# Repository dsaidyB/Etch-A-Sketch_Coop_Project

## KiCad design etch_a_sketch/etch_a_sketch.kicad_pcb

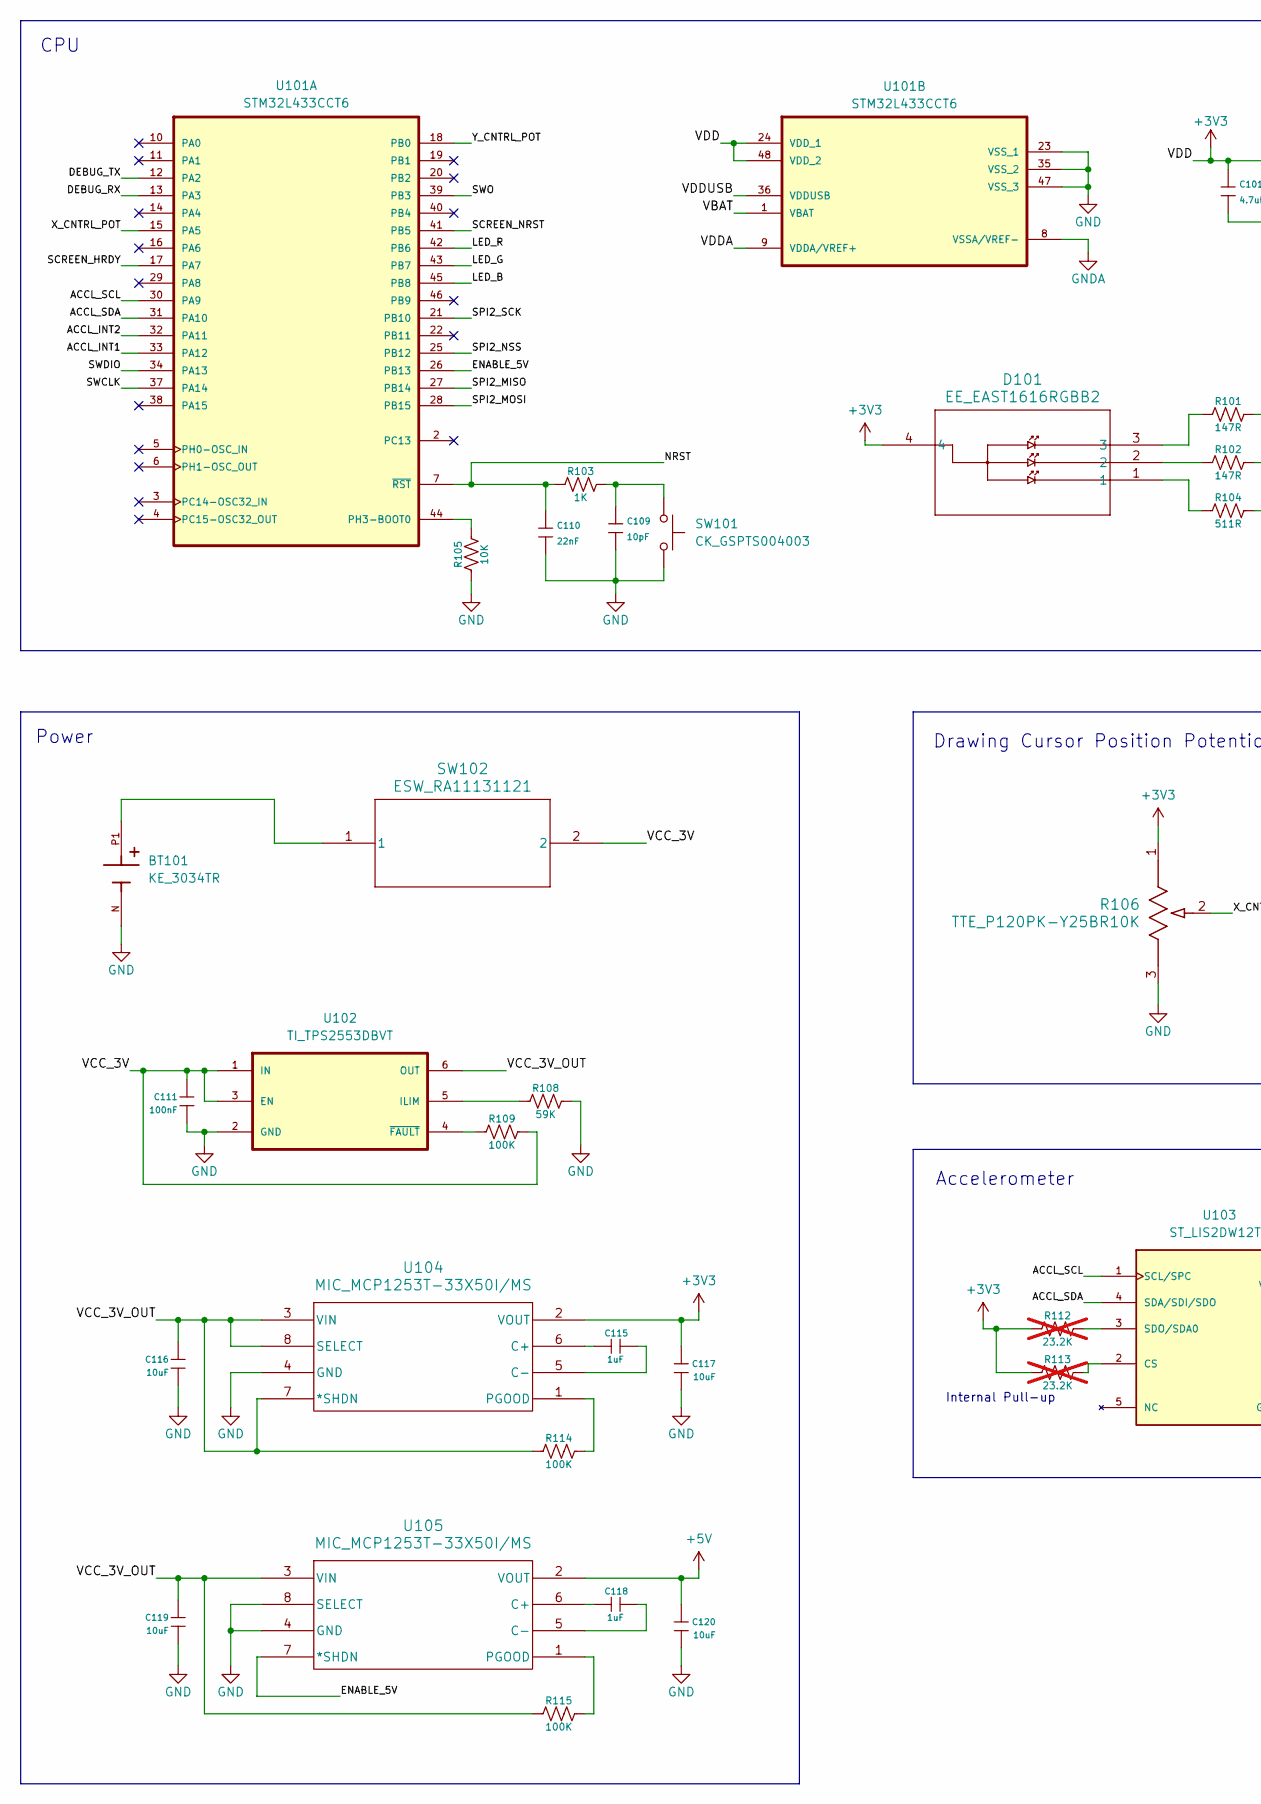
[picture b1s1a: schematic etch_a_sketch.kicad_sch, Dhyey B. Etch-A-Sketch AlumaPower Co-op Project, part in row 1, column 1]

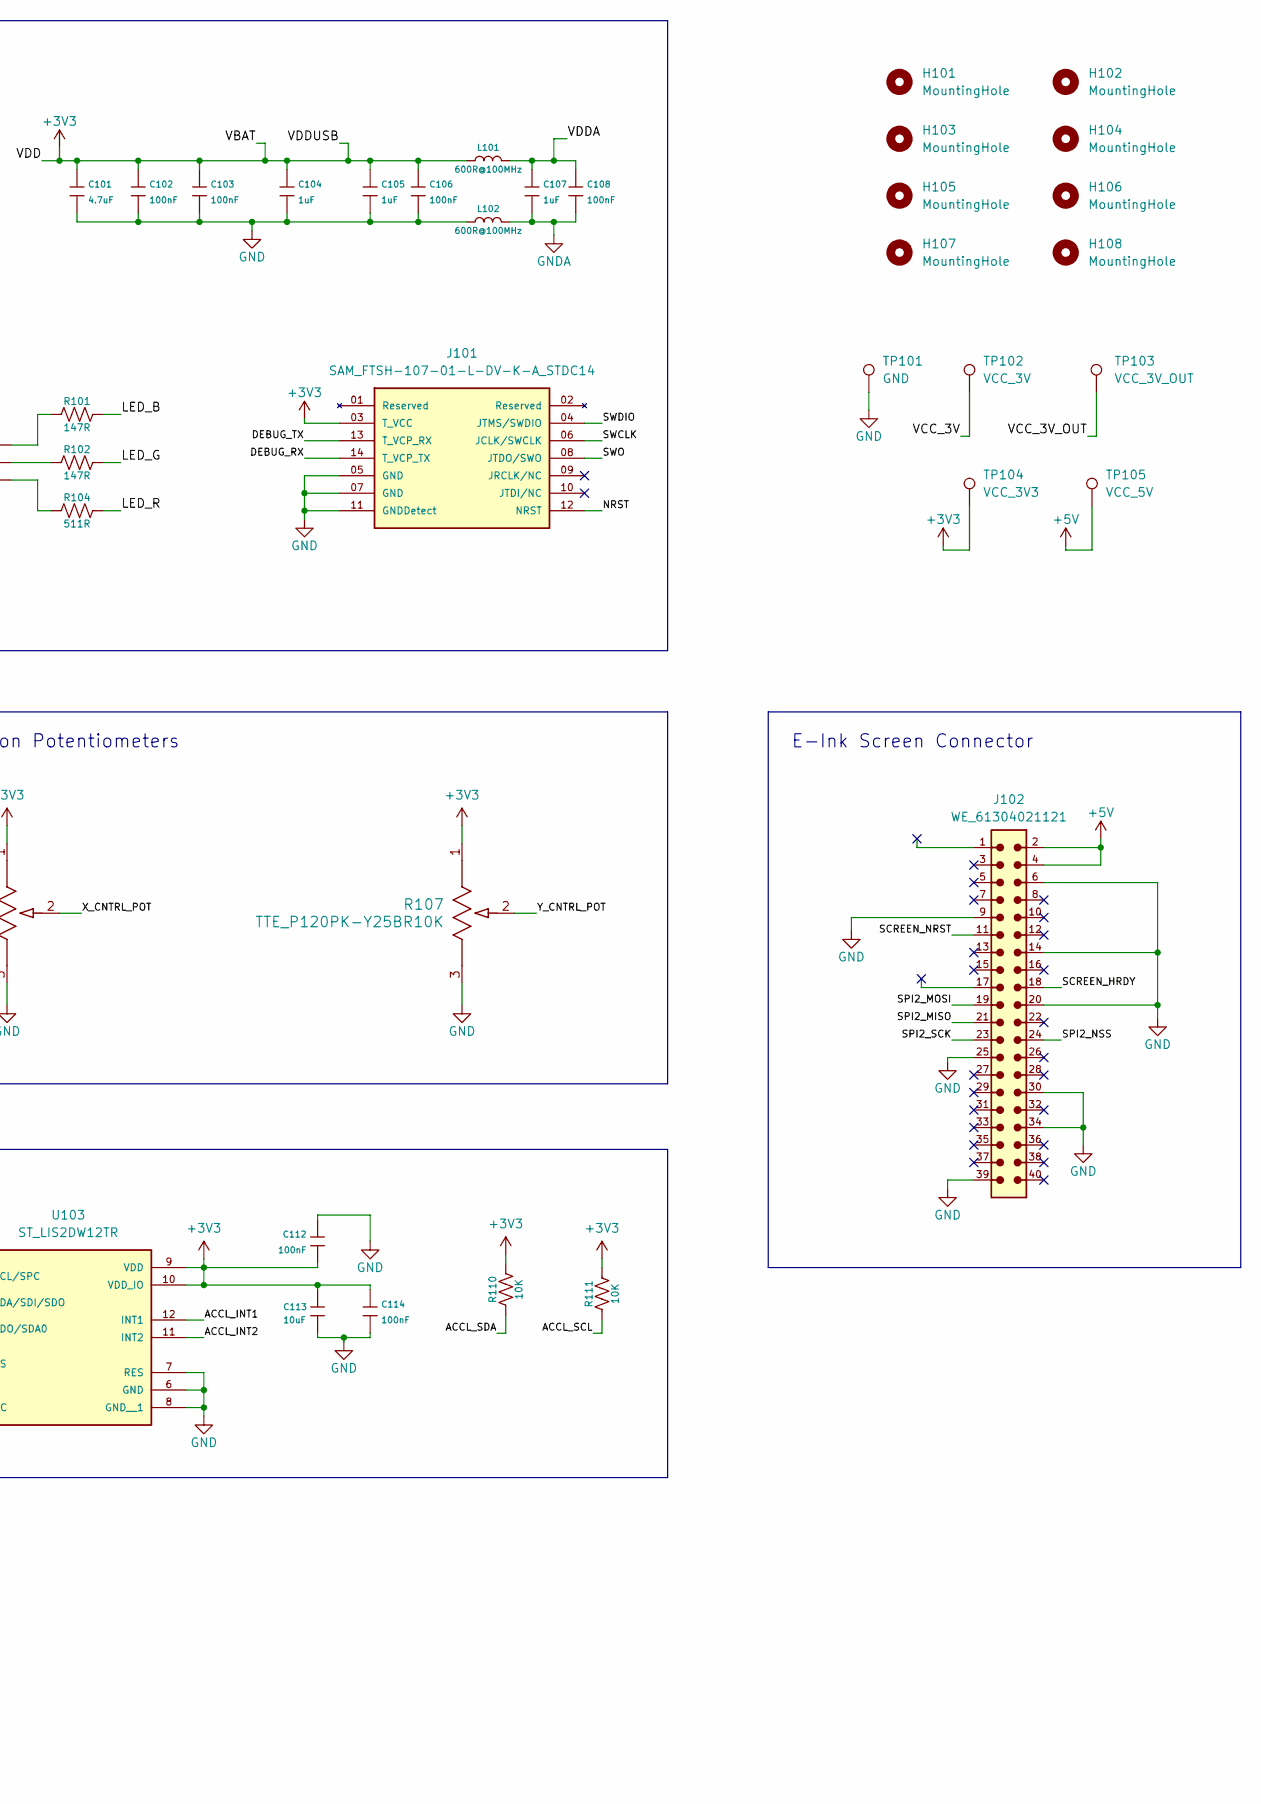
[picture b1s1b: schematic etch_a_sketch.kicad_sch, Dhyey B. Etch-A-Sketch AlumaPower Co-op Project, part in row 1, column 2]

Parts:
BT101: KE_3034TR; PARTREV E; DigiKey_Part_Number 36-3034CT-ND
C101: 4.7uF; 0603_1608Metric
C102, C103, C106, C108, C111, C112, C114: 100nF; 0603_1608Metric
C104, C105, C107, C115, C118: 1uF; 0603_1608Metric
C109: 10pF; 0402_1005Metric
C110: 22nF; 0603_1608Metric
C113, C116, C117, C119, C120: 10uF; 0603_1608Metric
D101: EE_EAST1616RGBB2
H101, H102, H103, H104, H105, H106, H107, H108: MountingHole; MountingHole_3.2mm_M3_ISO14580_Pad_TopBottom
J101: SAM_FTSH-107-01-L-DV-K-A_STDC14; PARTREV H; DigiKey_Part_Number FTSH-107-01-L-DV-K-A-ND
J102: WE_61304021121
L101, L102: 600R@100MHz; 0603_1608Metric
R101, R102: 147R; 0603_1608Metric
R103: 1K; 0603_1608Metric
R104: 511R; 0603_1608Metric
R105, R110, R111: 10K; 0603_1608Metric
R106, R107: TTE_P120PK-Y25BR10K
R108: 59K; 0603_1608Metric
R109, R114, R115: 100K; 0603_1608Metric
R112, R113: 23.2K; 0603_1608Metric; not fitted
SW101: CK_GSPTS004003
SW102: ESW_RA11131121
TP101: GND; TestPoint_THTPad_4.0x4.0mm_Drill2.0mm
TP102: VCC_3V; TestPoint_THTPad_4.0x4.0mm_Drill2.0mm
TP103: VCC_3V_OUT; TestPoint_THTPad_4.0x4.0mm_Drill2.0mm
TP104: VCC_3V3; TestPoint_THTPad_4.0x4.0mm_Drill2.0mm
TP105: VCC_5V; TestPoint_THTPad_4.0x4.0mm_Drill2.0mm
U101: STM32L433CCT6
U102: TI_TPS2553DBVT; TI_TPS2553DBVT_SOT-23-6; DigiKey_Part_Number 296-23990-1-ND
U103: ST_LIS2DW12TR; PARTREV 4
U104, U105: MIC_MCP1253T-33X50I/MS; MIC_MCP1253T-33X50IMS

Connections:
+3V3: C101.1, C102.1, C103.1, C104.1, C105.1, C106.1, C112.2, C113.2, C114.1, C117.2, D101.4, J101.03 (T_VCC), L101.1, R106.1, R107.1, R110.2, R111.2, R112.1, R113.1, TP104.1, U101.1 (VBAT), U101.24 (VDD_1), U101.36 (VDDUSB), U101.48 (VDD_2), U103.9 (VDD), U103.10 (VDD_IO), U104.2 (VOUT)
+5V: C120.2, J102.2, J102.4, TP105.1, U105.2 (VOUT)
/ACCL_INT1: U101.33 (PA12), U103.12 (INT1)
/ACCL_INT2: U101.32 (PA11), U103.11 (INT2)
/ACCL_SCL: R111.1, U101.30 (PA9), U103.1 (SCL/SPC)
/ACCL_SDA: R110.1, U101.31 (PA10), U103.4 (SDA/SDI/SDO)
/DEBUG_RX: J101.14 (T_VCP_TX), U101.13 (PA3)
/DEBUG_TX: J101.13 (T_VCP_RX), U101.12 (PA2)
/ENABLE_5V: U101.26 (PB13), U105.7 (*SHDN)
/LED_B: R101.2, U101.45 (PB8)
/LED_G: R102.2, U101.43 (PB7)
/LED_R: R104.2, U101.42 (PB6)
/NRST: C110.1, J101.12 (NRST), R103.1, U101.7 (~RST)
/SCREEN_HRDY: J102.18, U101.17 (PA7)
/SCREEN_NRST: J102.11, U101.41 (PB5)
/SPI2_MISO: J102.21, U101.27 (PB14)
/SPI2_MOSI: J102.19, U101.28 (PB15)
/SPI2_NSS: J102.24, U101.25 (PB12)
/SPI2_SCK: J102.23, U101.21 (PB10)
/SWCLK: J101.06 (JCLK/SWCLK), U101.37 (PA14)
/SWDIO: J101.04 (JTMS/SWDIO), U101.34 (PA13)
/SWO: J101.08 (JTDO/SWO), U101.39 (PB3)
/VCC_3V: C111.2, R109.2, SW102.2, TP102.1, U102.1 (IN), U102.3 (EN)
/VCC_3V_OUT: C116.2, C119.2, R114.1, R115.1, TP103.1, U102.6 (OUT), U104.3 (VIN), U104.7 (*SHDN), U104.8 (SELECT), U105.3 (VIN)
/VDDA: C107.1, C108.1, L101.2, U101.9 (VDDA/VREF+)
/X_CNTRL_POT: R106.2, U101.15 (PA5)
/Y_CNTRL_POT: R107.2, U101.18 (PB0)
GND: BT101.N, C101.2, C102.2, C103.2, C104.2, C105.2, C106.2, C109.2, C110.2, C111.1, C112.1, C113.1, C114.2, C116.1, C117.1, C119.1, C120.1, J101.05 (GND), J101.07 (GND), J101.11 (GNDDetect), J102.6, J102.9, J102.14, J102.20, J102.25, J102.30, J102.34, J102.39, L102.1, R105.1, R106.3, R107.3, R108.2, SW101.2, TP101.1, U101.23 (VSS_1), U101.35 (VSS_2), U101.47 (VSS_3), U102.2 (GND), U103.6 (GND), U103.7 (RES), U103.8 (GND__1), U104.4 (GND), U105.4 (GND), U105.8 (SELECT)
GNDA: C107.2, C108.2, L102.2, U101.8 (VSSA/VREF-)
unnamed: BT101.P1, BT101.P2, SW102.1
unnamed: C109.1, R103.2, SW101.1
unnamed: D101.1, R104.1
unnamed: D101.2, R102.1
unnamed: D101.3, R101.1
unnamed: R105.2, U101.44 (PH3-BOOT0)
unnamed: R108.1, U102.5 (ILIM)
unnamed: R109.1, U102.4 (~FAULT)
unnamed: R113.2, U103.2 (CS)
unnamed: R112.2, U103.3 (SDO/SDA0)
unnamed: C115.1, U104.6 (C+)
unnamed: C115.2, U104.5 (C-)
unnamed: R114.2, U104.1 (PGOOD)
unnamed: C118.1, U105.6 (C+)
unnamed: C118.2, U105.5 (C-)
unnamed: R115.2, U105.1 (PGOOD)

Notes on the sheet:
Internal Pull-up
Drawing Cursor Position Potentiometers
Accelerometer
CPU
Power
E-Ink Screen Connector

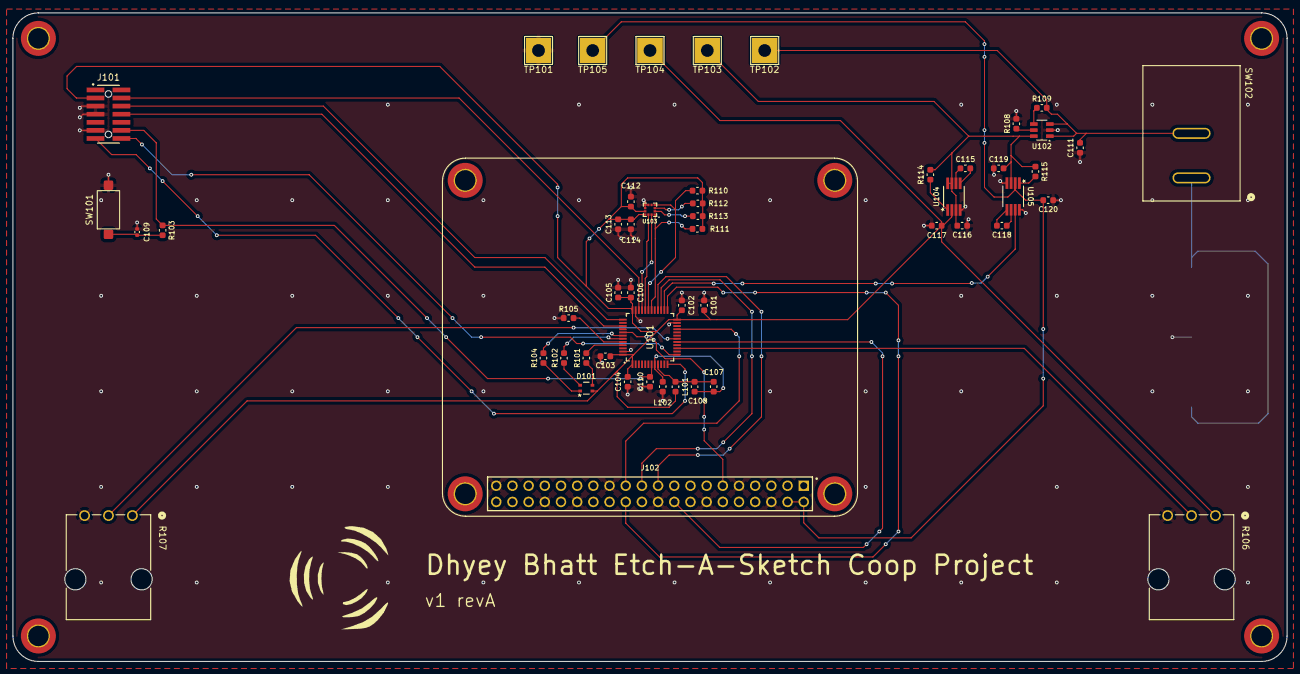
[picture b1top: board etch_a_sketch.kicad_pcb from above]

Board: 2 copper layers, 200.0 x 101.8 mm, 61 parts (1 on the bottom side), 45 nets.

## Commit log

2025-12-12 revA done
2025-12-12 started BOM
2025-12-12 BOM done
2025-12-15 updated bom
2026-01-01 v1 of driver
